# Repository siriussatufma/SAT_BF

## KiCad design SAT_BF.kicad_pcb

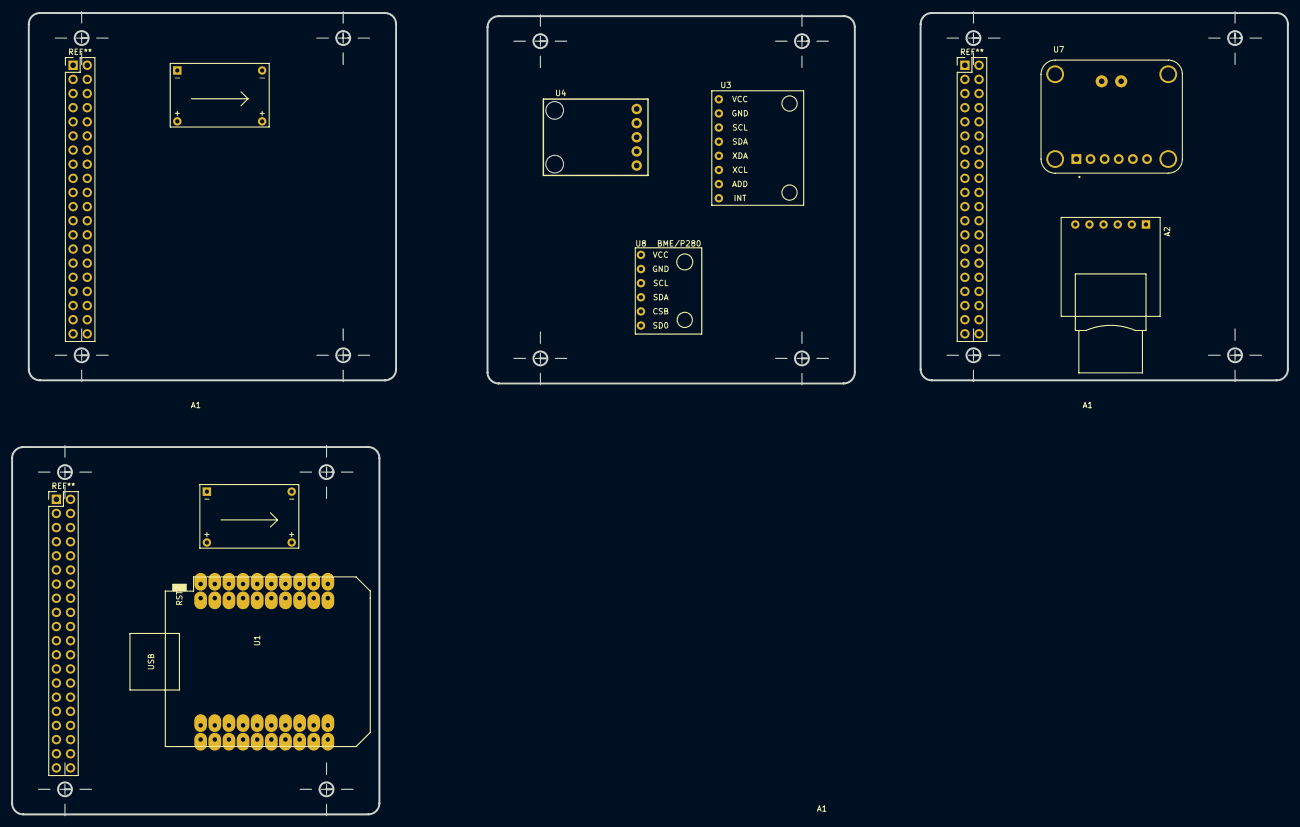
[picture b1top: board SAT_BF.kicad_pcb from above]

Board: 2 copper layers, 229.2 x 144.5 mm, 8 parts (0 on the bottom side), 10 nets, no tracks yet.

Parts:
A1, A1#2: Mini360_Module
A2: SD_Card_Module
U1: esp32-wemos-d1-mini
U3: module_mpu6050
U4: HMC5883L
U7: INA219; MODULE_INA219
U8: module_bme280

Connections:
/3V3: A2.1 (3V3), U1.16 (3V3), U3.1 (VCC), U4.1 (VCC), U7.1 (VCC), U7.5 (VIN-), U7.VIN-, U8.1 (VCC)
/CS_SDCARD: A2.2 (CS), U1.18 (IO_13/TCK)
/GND: A1.4 (OUT-), A1#2.4 (OUT-), A2.6 (GND), U1.1 (GND), U1.22 (GND), U1.33 (GND), U3.2 (GND), U4.2 (GND), U7.2 (GND), U8.2 (GND)
/I2C_SCL_1: U1.25 (IO_22/D1/SCL), U3.3 (SCL), U4.3 (SCL), U7.3 (SCL), U8.3 (SCL)
/I2C_SDA_1: U1.27 (IO_21/D2/SDA), U3.4 (SDA), U4.4 (SDA), U7.4 (SDA), U8.4 (SDA)
/SPI_MISO_1: A2.5 (MISO), U1.10 (IO_19/D6)
/SPI_SCK_1: A2.4 (CLK), U1.8 (IO_18/D5)
unnamed: A1.1 (IN+), A1#2.1 (IN+)
unnamed: A1.2 (IN-), A1#2.2 (IN-)
unnamed: A1.3 (OUT+), A1#2.3 (OUT+), U7.6 (VIN+), U7.VIN+
